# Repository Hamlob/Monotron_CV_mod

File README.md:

# Monotron_CV_mod
A modification for Korg's Monotron Delay, which makes it accept standard Eurorack CV voltages (Pitch, Gate and Cutoff CV). The mod also provides an option to power the monotron via micro-USB.
<br />
<br />
Input specs:<br />
Pitch CV: 1V/oct (0-10V) <br />
Gate CV: GATE ON-> 5-12V <br />
Cutoff CV: 0-10Vpp (possibly more if you attenuate the signal using the Cutoff Trimmer, but it can damage the op-amp if the trimmer is in the wrong position).
<br />
<br />
Micro-usb: 5 +/- 10%

Output:<br />
Connect GATE, VCC, GND, CUTOFF and LFO testpads of Monotron to GATE, +5V, GND, CUTOFF and LFO pins of the mod PCB respectively, by soldering wires between them.<br />
GATE and CUTOFF are output signals being provided by the mod PCB. LFO is an input signal generated on the monotron board and routed into the mod PCB, which includes a proper output jack.
<br />
<br />
If you wish to use USB power, you need to cut the track as shown on Figure 1 to disconnect the batteries from Vcc. Then you need to solder a wire from the positive lead of the capacitor to the Bat pin of the mod PCB (Figure 2). This is done to prevent current flowing from USB to the batteries, potentionally damaging them (Figure 3).
<br />
<br />
Figure 1: <br />

<br />
<br />
Figure 2: <br />

<br />
Figure 3: <br />

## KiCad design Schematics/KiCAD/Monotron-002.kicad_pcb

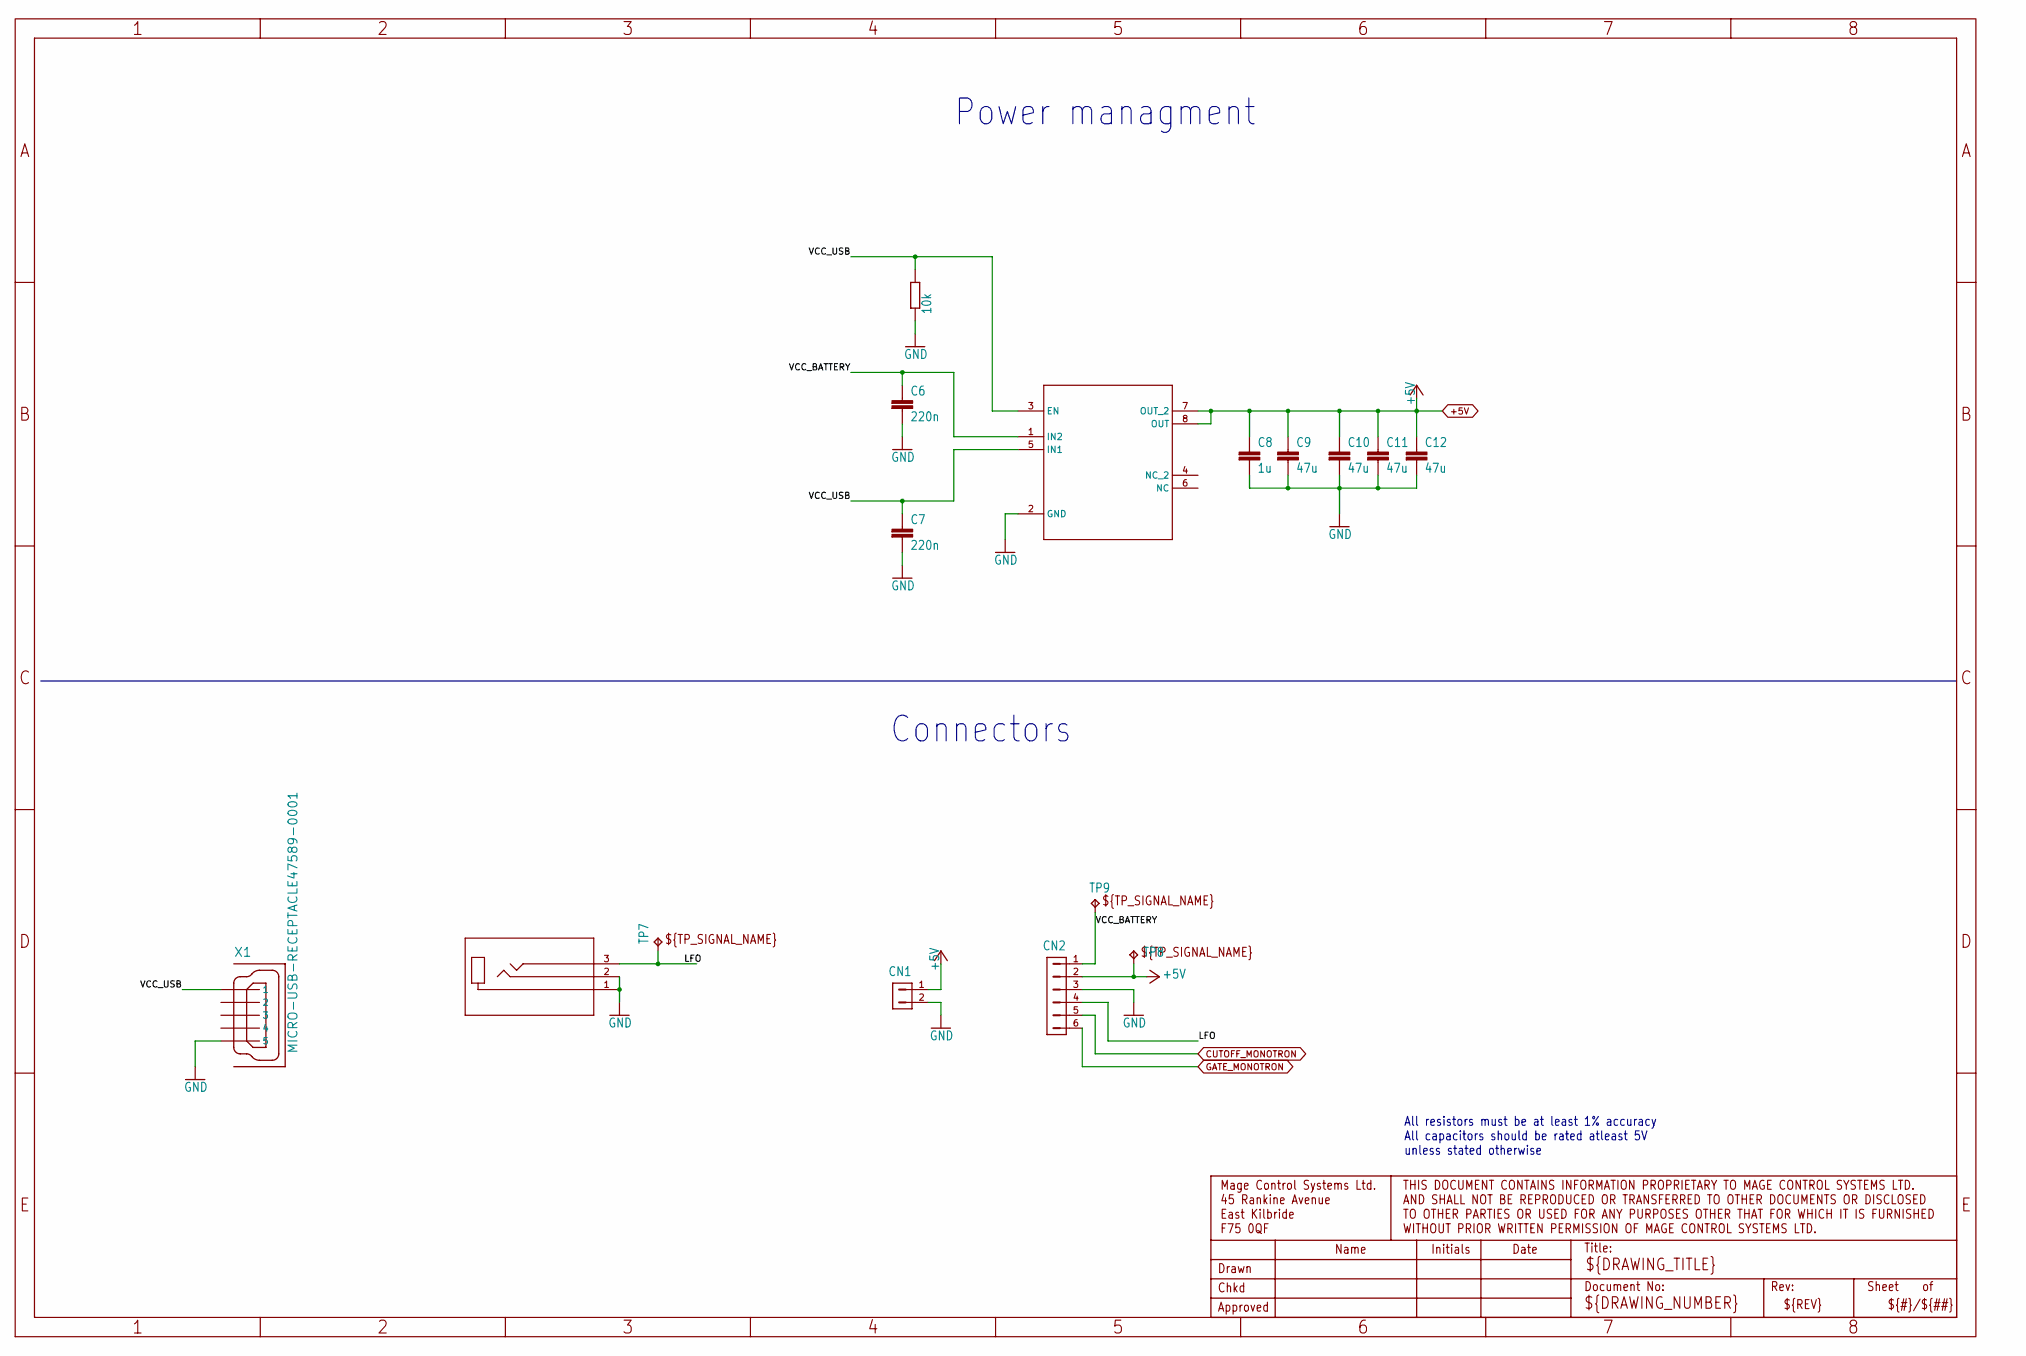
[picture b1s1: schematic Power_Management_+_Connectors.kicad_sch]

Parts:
C6, C7: 220n; C0603
C8: 1u; C0603
C9, C10, C11, C12: 47u; C0805
CN1: HDR-1X2-SIP-100; SIP-100-2V
CN2: HDR-1X6-SIP-100; SIP-100-6V
J4: STX-3000; STX-3000_KYC
R21: 10k; R0603
TP7, TP8, TP9: TPB1,27; B1,27
U1: TPS2105D; D8
X1: MICRO-USB-RECEPTACLE47589-0001; 47589-0001

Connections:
+5V: C8.1, C9.1, C10.1, C11.1, C12.1, CN1.1, CN2.2, TP8.TP, U1.7 (OUT_2), U1.8 (OUT); also elsewhere on the board
CUTOFF_MONOTRON: CN2.5; also elsewhere on the board
GATE_MONOTRON: CN2.6; also elsewhere on the board
GND: C6.2, C7.2, C8.2, C9.2, C10.2, C11.2, C12.2, CN1.2, CN2.3, J4.1, J4.2, R21.1, U1.2 (GND), X1.5; also elsewhere on the board
LFO: CN2.4, J4.3, TP7.TP
VCC_BATTERY: C6.1, CN2.1, TP9.TP, U1.1 (IN2)
VCC_USB: C7.1, R21.2, U1.3 (EN), U1.5 (IN1), X1.1

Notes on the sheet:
Power managment
Connectors
All resistors must be at least 1% accuracy All capacitors should be rated atleast 5V unless stated otherwise

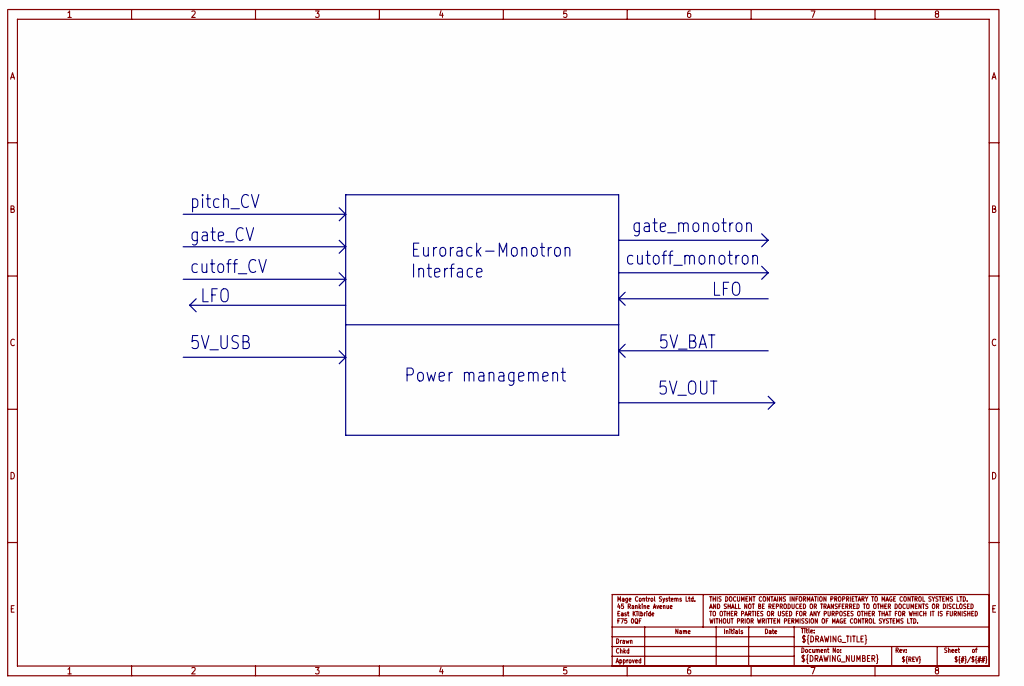
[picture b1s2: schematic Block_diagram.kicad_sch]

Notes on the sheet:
Power management
5V_USB
Eurorack-Monotron Interface
gate_CV
gate_monotron
LFO
pitch_CV
5V_OUT
cutoff_CV
cutoff_monotron
5V_BAT

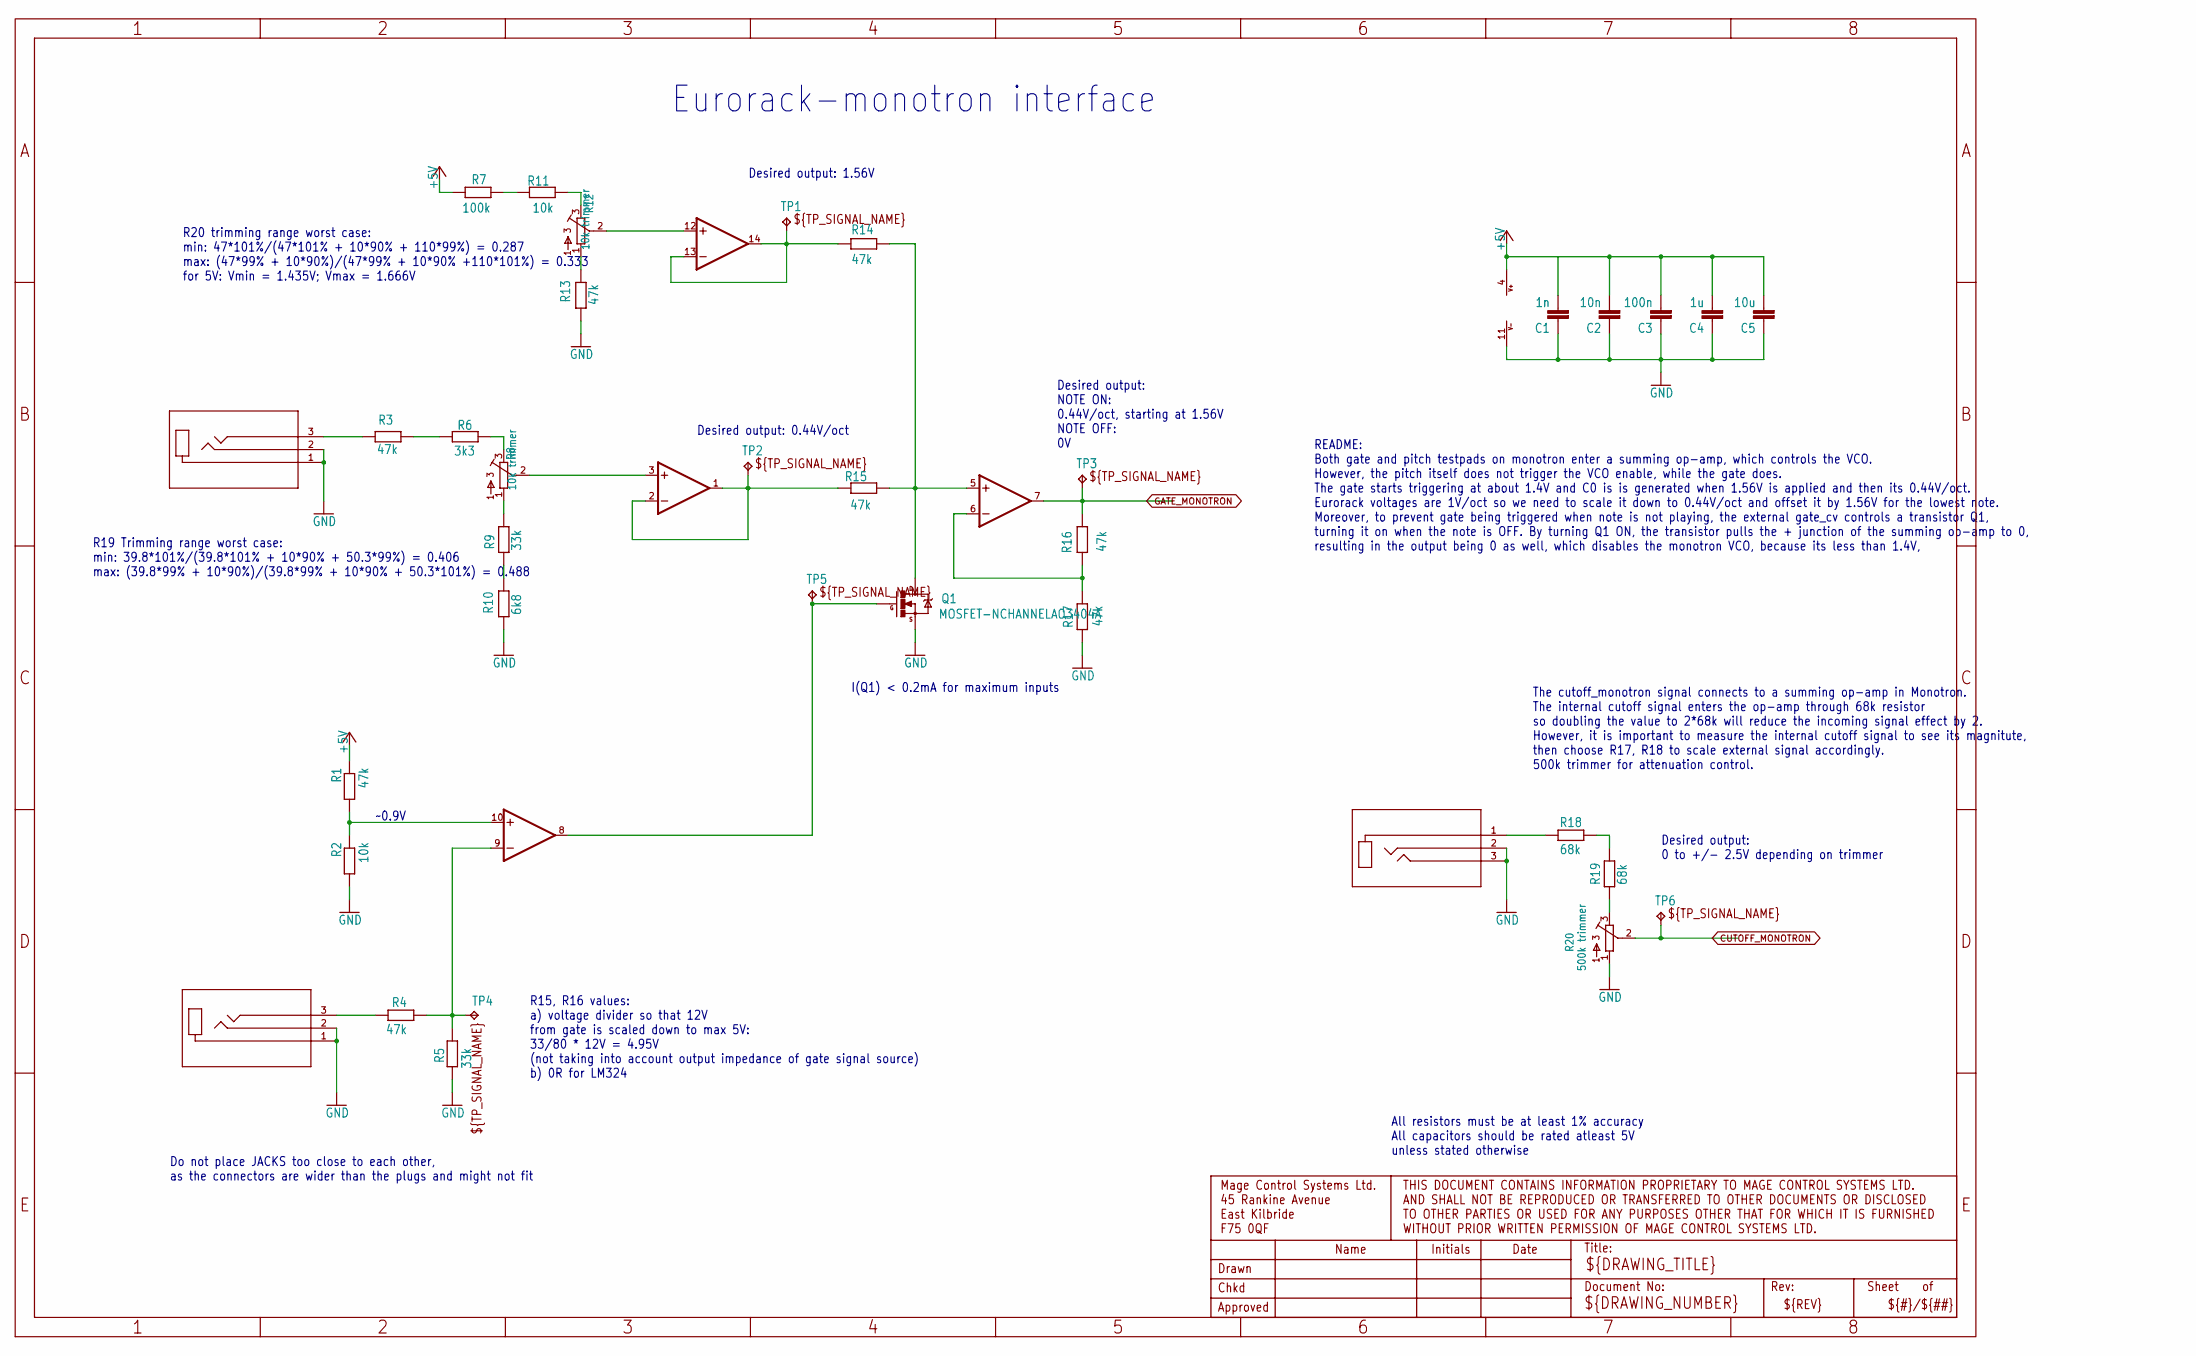
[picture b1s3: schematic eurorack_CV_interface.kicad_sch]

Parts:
C1: 1n; C0603
C2: 10n; C0603
C3: 100n; C0603
C4: 1u; C0603
C5: 10u; C0805
IC1: LM324D; SO14
J1, J2, J3: STX-3000; STX-3000_KYC
Q1: MOSFET-NCHANNELAO3404A; SOT23-3
R1, R3, R4, R13, R14, R15, R16, R17: 47k; R0603
R2, R11: 10k; R0603
R5, R9: 33k; R0603
R6: 3k3; R0603
R7: 100k; R0603
R8, R12: 10k trimmer; 3362R
R10: 6k8; R0603
R18, R19: 68k; R0603
R20: 500k trimmer; 3362R
TP1, TP2, TP3, TP4, TP5, TP6: TPB1,27; B1,27

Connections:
+5V: C1.2, C2.2, C3.2, C4.2, C5.2, IC1.4 (V+), R1.1, R7.2; also elsewhere on the board
CUTOFF_MONOTRON: R20.2, TP6.TP; also elsewhere on the board
GATE_MONOTRON: IC1.7 (OUT), R16.1, TP3.TP; also elsewhere on the board
GND: C1.1, C2.1, C3.1, C4.1, C5.1, IC1.11 (V-), J1.1, J1.2, J2.1, J2.2, J3.2, J3.3, Q1.2 (S), R2.2, R5.2, R10.1, R13.1, R17.2, R20.1; also elsewhere on the board
unnamed: R3.2, R6.2
unnamed: R9.1, R10.2
unnamed: IC1.1 (OUT), IC1.2 (-IN), R15.2, TP2.TP
unnamed: J1.3, R3.1
unnamed: IC1.5 (+IN), Q1.3 (D), R14.1, R15.1
unnamed: IC1.12 (+IN), R12.2
unnamed: J3.1, R18.2
unnamed: R18.1, R19.2
unnamed: R19.1, R20.3
unnamed: R8.1, R9.2
unnamed: IC1.8 (OUT), Q1.1 (G), TP5.TP
unnamed: R6.1, R8.3
unnamed: IC1.3 (+IN), R8.2
unnamed: R12.1, R13.2
unnamed: R11.1, R12.3
unnamed: R7.1, R11.2
unnamed: J2.3, R4.2
unnamed: IC1.9 (-IN), R4.1, R5.1, TP4.TP
unnamed: IC1.10 (+IN), R1.2, R2.1
unnamed: IC1.13 (-IN), IC1.14 (OUT), R14.2, TP1.TP
unnamed: IC1.6 (-IN), R16.2, R17.1

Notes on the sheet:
Desired output: 1.56V
R15, R16 values: a) voltage divider so that 12V from gate is scaled down to max 5V: 33/80 * 12V = 4.95V (not taking into account output impedance of gate signal source) b) 0R for LM324
All resistors must be at least 1% accuracy All capacitors should be rated atleast 5V unless stated otherwise
R20 trimming range worst case: min: 47*101%/(47*101% + 10*90% + 110*99%) = 0.287 max: (47*99% + 10*90%)/(47*99% + 10*90% +110*101%) = 0.333 for 5V: Vmin = 1.435V; Vmax = 1.666V
The cutoff_monotron signal connects to a summing op-amp in Monotron. The internal cutoff signal enters the op-amp through 68k resistor so doubling the value to 2*68k will reduce the incoming signal effect by 2. However, it is important to measure the internal cutoff signal to see its magnitute, the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
I(Q1) < 0.2mA for maximum inputs
README: Both gate and pitch testpads on monotron enter a summing op-amp, which controls the VCO. However, the pitch itself does not trigger the VCO enable, while the gate does. The gate starts triggering at about 1.4V and C0 is is generated when 1.56V is applied and then its 0.44V/oct. Eurorack vol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
Desired output: 0 to +/- 2.5V depending on trimmer
Desired output: 0.44V/oct
Eurorack-monotron interface
~0.9V
Do not place JACKS too close to each other, as the connectors are wider than the plugs and might not fit
Desired output: NOTE ON: 0.44V/oct, starting at 1.56V NOTE OFF: 0V
R19 Trimming range worst case: min: 39.8*101%/(39.8*101% + 10*90% + 50.3*99%) = 0.406 max: (39.8*99% + 10*90%)/(39.8*99% + 10*90% + 50.3*101%) = 0.488

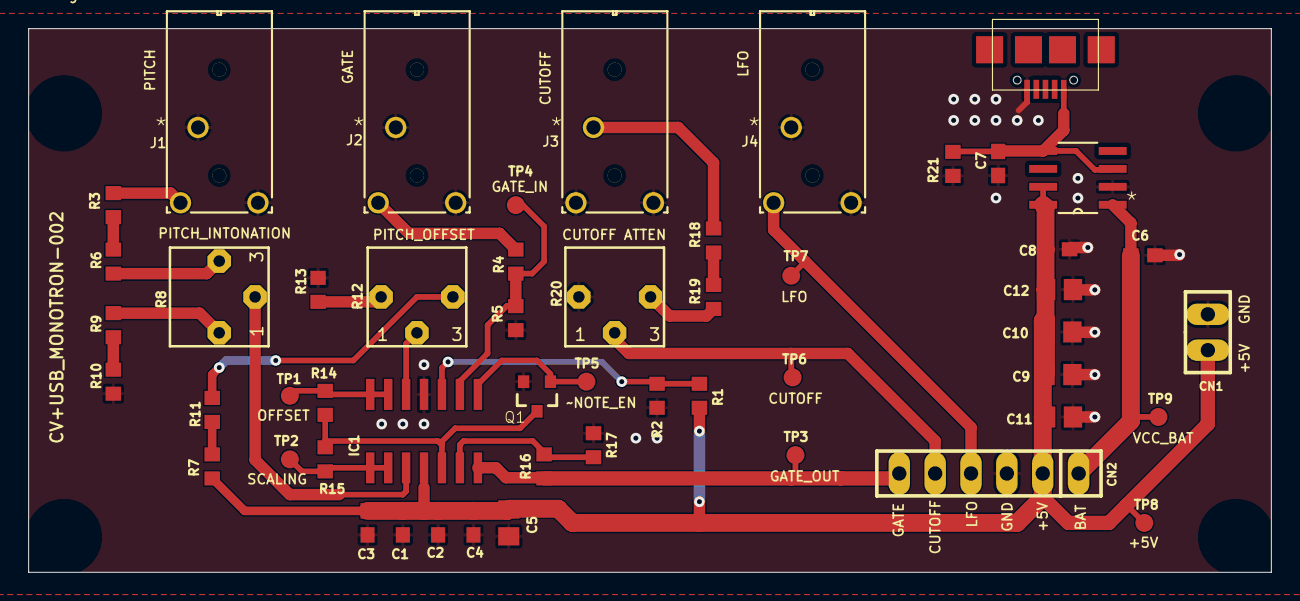
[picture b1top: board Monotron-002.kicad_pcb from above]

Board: 2 copper layers, 88.0 x 38.5 mm, 52 parts (0 on the bottom side), 28 nets.

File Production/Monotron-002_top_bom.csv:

Comment,Designator,Footprint,LCSC Part #
1n,C1,C0603,
1u,C4 C8,C0603,
3k3,R6,R0603,
6k8,R10,R0603,
10k,R11 R21,R0603,
10n,C2,C0603,
10u,C5,C0805,
33k,R5 R9,R0603,
47k,R1 R2 R3 R4 R13 R14 R15 R16 R17,R0603,
47u,C9 C10 C11 C12,C0805,
68k,R18 R19,R0603,
100k,R7,R0603,
100n,C3,C0603,
220n,C6 C7,C0603,
LM324D,IC1,SO14,
MICRO-USB-RECEPTACLE47589-0001,X1,47589-0001,
N-MOSFET,Q1,SOT23-3,
TPB1 27,TP1,B1 27,
TPB1 27,TP2,B1 27,
TPB1 27,TP3,B1 27,
TPB1 27,TP4,B1 27,
TPB1 27,TP5,B1 27,
TPB1 27,TP6,B1 27,
TPB1 27,TP7,B1 27,
TPB1 27,TP8,B1 27,
TPB1 27,TP9,B1 27,
TPS2105D,U1,D8,

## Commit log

2022-04-19 Update README.md
    Initialized readme
2022-04-19 Create blank
2022-04-19 Schematic
2022-04-19 Delete blank
    Dummy file
2022-04-19 Create dummy
2022-04-19 Add files via upload
    Bom, CPL, datasheet folder and gerbers
2022-04-19 Delete dummy
    dummy file
2022-04-19 Add files via upload
    Eagle files
2022-04-19 Add files via upload
    additional datasheets
2023-10-29 updated schematics and brd files
2023-10-29 updated schem pdf
2023-11-19 added kicad files
2024-01-02 updated schematic
    corrected cutoff connector wiring and cutoff trimmer disconnected from GND
2024-01-02 updated eagle files
    corrected cutoff connector wiring and cutoff trimmer disconnected from GND
2024-01-02 updated gerbers
    gerbers with corrected cutoff connector and cutoff trimmer

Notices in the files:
parts and their libraries:
(C) 2014 Tomasz Boleslaw CEDRO, cederom@tlen.pl, http://www.tomek.cedro.info.
